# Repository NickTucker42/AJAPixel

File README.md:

# AJAPixel
Yes, another WLED Controller

If you have not heard about WLED then please check out this page:
https://github.com/Aircoookie/WLED

This board will come with WLED preinstalled and is available on my Tindie store:
https://www.tindie.com/stores/nicktucker42/

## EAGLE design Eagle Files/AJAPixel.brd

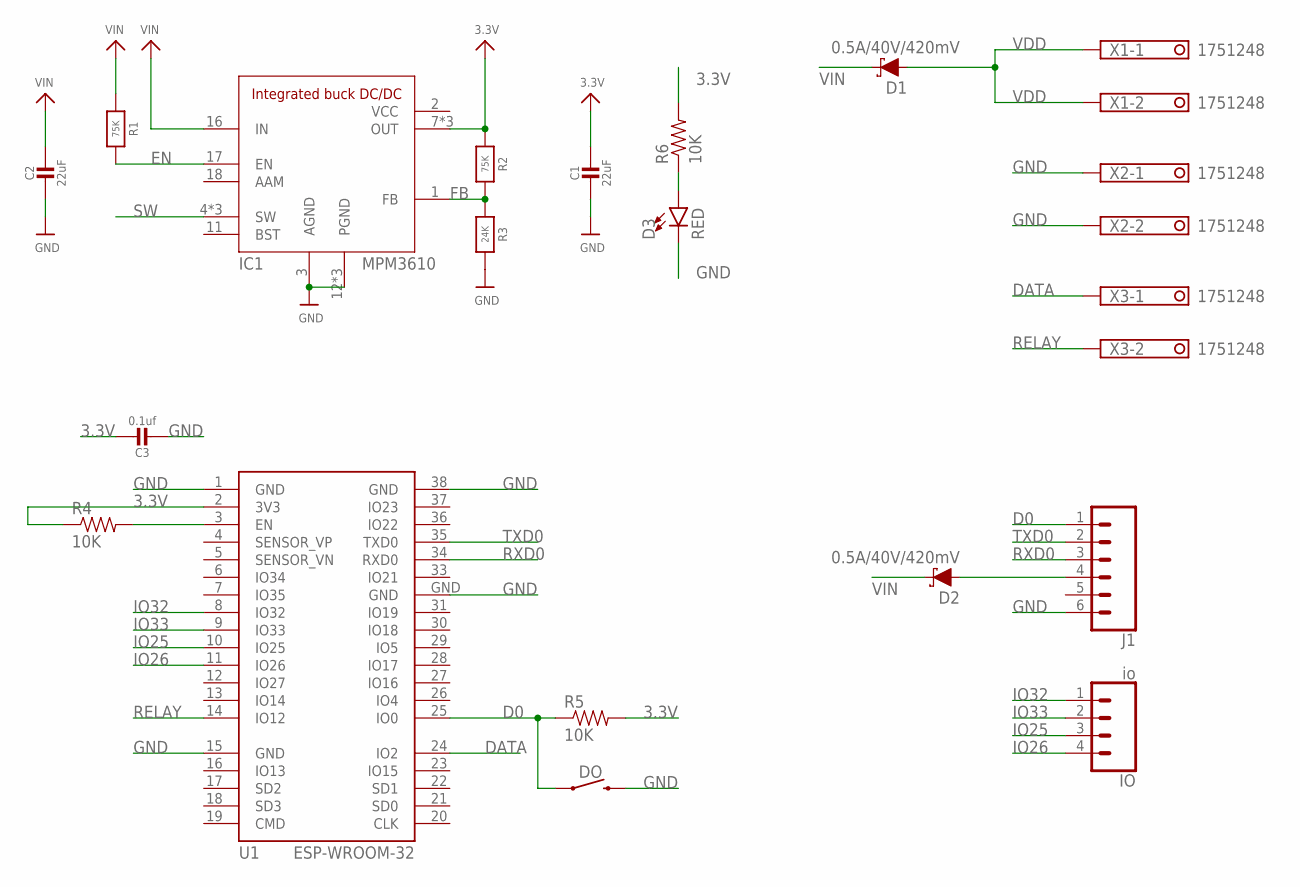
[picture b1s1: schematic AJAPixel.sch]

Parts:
C1, C2: 22uF; 0805-NO
C3: 0.1uf; _0603
D1, D2: 0.5A/40V/420mV; SOD-323
D3: RED; LED-0603
DO: MOMENTARY-SWITCH-SPST-SMD-5.2MM; TACTILE_SWITCH_SMD_5.2MM
IC1: MPM3610
IO: io; 1X04
J1: CONN_06SILK_FEMALE_PTH; 1X06
R1, R2: 75K; 0603-NO
R3: 24K; 0603-NO
R4, R5, R6: 10K; 0603
U1: ESP-WROOM-32
X1, X2, X3: 1751248

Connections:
3.3V: C1.1, C3.1, IC1.7 (OUT), IC1.8 (OUT), IC1.9 (OUT), R2.1, R4.1, R5.2, R6.2, U1.2 (3V3)
D0: DO.1, J1.1, R5.1, U1.25 (IO0)
DATA: U1.24 (IO2), X3.1
EN: IC1.17 (EN), R1.2
FB: IC1.1 (FB), R2.2, R3.1
GND: C1.2, C2.2, C3.2, D3.C, DO.3 (2), IC1.3 (AGND), IC1.12 (PGND), IC1.13 (PGND), IC1.14 (PGND), J1.6, R3.2, U1.1 (GND), U1.15 (GND), U1.38 (GND), U1.GND, X2.1, X2.2
IO25: IO.3, U1.10 (IO25)
IO26: IO.4, U1.11 (IO26)
IO32: IO.1, U1.8 (IO32)
IO33: IO.2, U1.9 (IO33)
unnamed: D3.A, R6.1
unnamed: D2.A, J1.4
unnamed: R4.2, U1.3 (EN)
RELAY: U1.14 (IO12), X3.2
RXD0: J1.3, U1.34 (RXD0)
SW: IC1.4 (SW), IC1.5 (SW), IC1.6 (SW)
TXD0: J1.2, U1.35 (TXD0)
VCC: IC1.2 (VCC)
VDD: D1.A, X1.1, X1.2
VIN: C2.1, D1.C, D2.C, IC1.16 (IN), R1.1

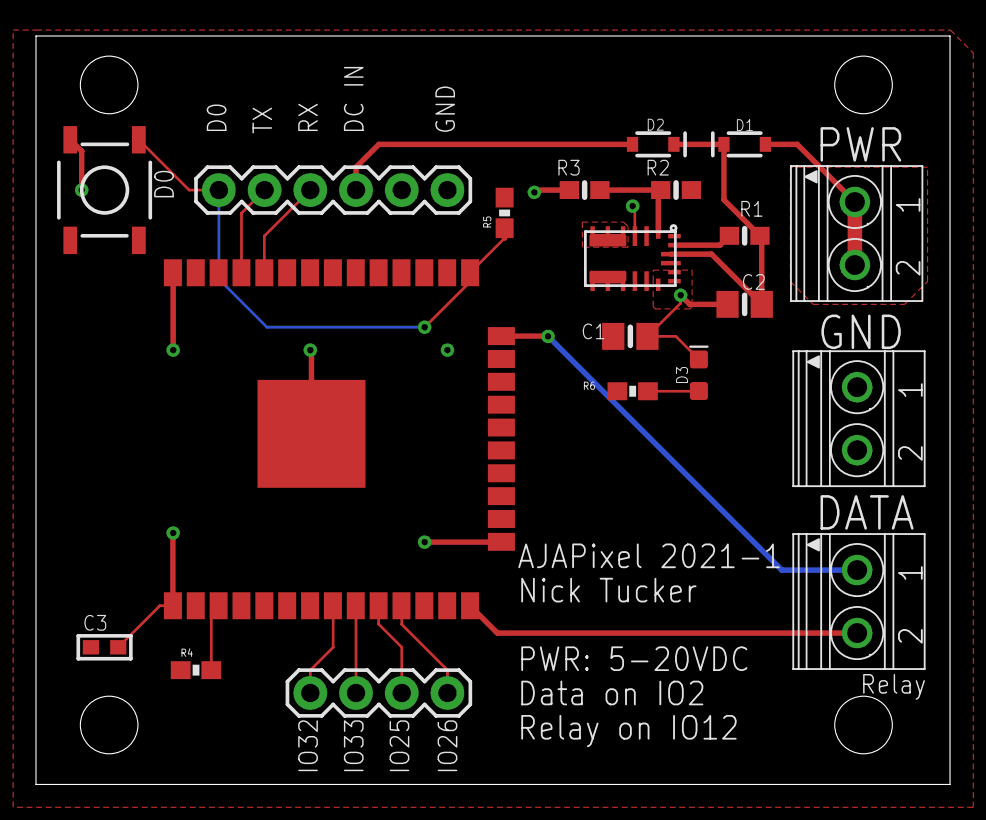
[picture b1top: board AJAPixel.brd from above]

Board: 2 copper layers, 50.8 x 41.6 mm, 20 parts (0 on the bottom side), 19 nets.

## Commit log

2021-05-20 Add files via upload
    V1 Board

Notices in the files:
parts and their libraries:
microbuilder: This work is placed in the public domain, and may be freely used for commercial and non-commercial work with the following conditions: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
SparkFun-Connectors: Licensing: Creative Commons ShareAlike 4.0 International - https://creativecommons.org/licenses/by-sa/4.0
